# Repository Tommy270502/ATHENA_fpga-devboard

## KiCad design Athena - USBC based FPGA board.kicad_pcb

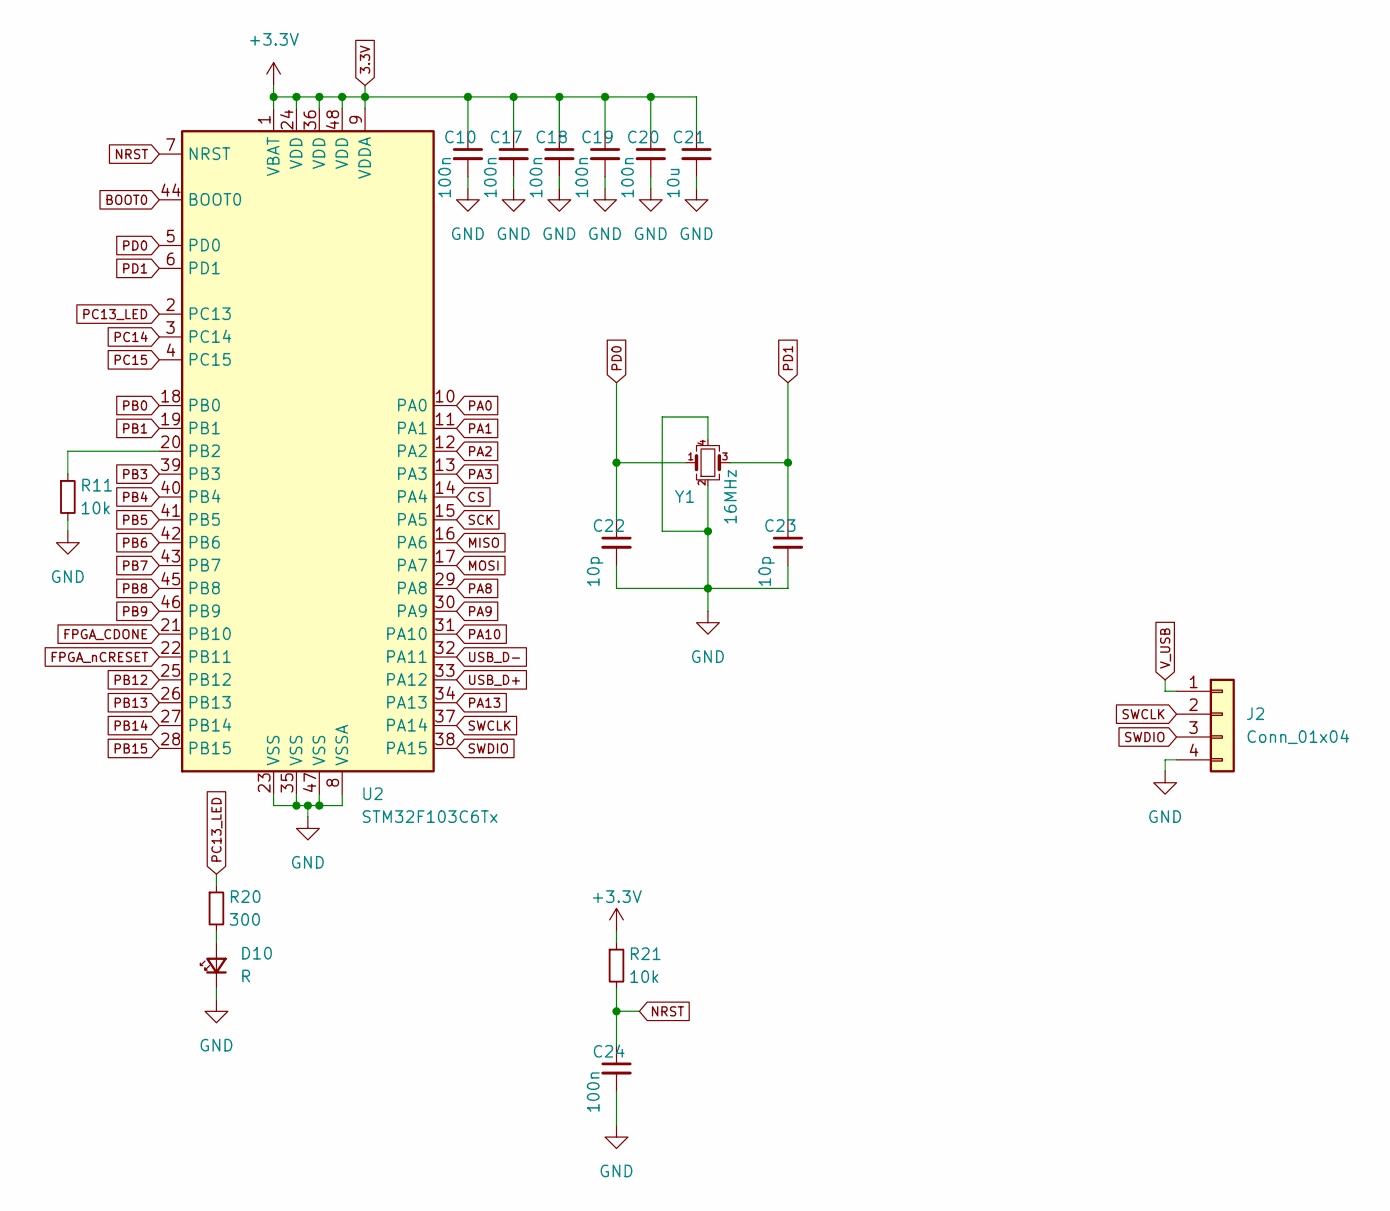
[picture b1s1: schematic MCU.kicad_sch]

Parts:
C10, C17, C18, C19, C20, C24: 100n; C_0603_1608Metric_Pad1.08x0.95mm_HandSolder
C21: 10u; C_0603_1608Metric_Pad1.08x0.95mm_HandSolder
C22, C23: 10p; C_0603_1608Metric_Pad1.08x0.95mm_HandSolder
D10: R; LED_0603_1608Metric_Pad1.05x0.95mm_HandSolder
J2: Conn_01x04; PinHeader_1x04_P2.54mm_Vertical
R11, R21: 10k; R_0603_1608Metric_Pad0.98x0.95mm_HandSolder
R20: 300; R_0603_1608Metric_Pad0.98x0.95mm_HandSolder
U2: STM32F103C6Tx; LQFP-48_7x7mm_P0.5mm
Y1: 16MHz; Crystal_SMD_2520-4Pin_2.5x2.0mm

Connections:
3.3V: C10.1, C17.1, C18.1, C19.1, C20.1, C21.1, R21.1, U2.1 (VBAT), U2.9 (VDDA), U2.24 (VDD), U2.36 (VDD), U2.48 (VDD); also elsewhere on the board
BOOT0: U2.44 (BOOT0)
CS: U2.14 (PA4); also elsewhere on the board
FPGA_CDONE: U2.21 (PB10); also elsewhere on the board
FPGA_nCRESET: U2.22 (PB11); also elsewhere on the board
GND: C10.2, C17.2, C18.2, C19.2, C20.2, C21.2, C22.2, C23.2, C24.2, D10.1 (K), J2.4, R11.2, U2.8 (VSSA), U2.23 (VSS), U2.35 (VSS), U2.47 (VSS), Y1.2, Y1.4; also elsewhere on the board
MISO: U2.16 (PA6); also elsewhere on the board
MOSI: U2.17 (PA7); also elsewhere on the board
NRST: C24.1, R21.2, U2.7 (NRST)
unnamed: D10.2 (A), R20.2
unnamed: R11.1, U2.20 (PB2)
PA0: U2.10 (PA0)
PA1: U2.11 (PA1)
PA2: U2.12 (PA2)
PA3: U2.13 (PA3)
PA8: U2.29 (PA8)
PA9: U2.30 (PA9)
PA10: U2.31 (PA10)
PA13: U2.34 (PA13)
PB0: U2.18 (PB0)
PB1: U2.19 (PB1)
PB3: U2.39 (PB3)
PB4: U2.40 (PB4)
PB5: U2.41 (PB5)
PB6: U2.42 (PB6)
PB7: U2.43 (PB7)
PB8: U2.45 (PB8)
PB9: U2.46 (PB9)
PB12: U2.25 (PB12)
PB13: U2.26 (PB13)
PB14: U2.27 (PB14)
PB15: U2.28 (PB15)
PC13_LED: R20.1, U2.2 (PC13)
PC14: U2.3 (PC14)
PC15: U2.4 (PC15)
PD0: C22.1, U2.5 (PD0), Y1.1
PD1: C23.1, U2.6 (PD1), Y1.3
SCK: U2.15 (PA5); also elsewhere on the board
SWCLK: J2.2, U2.37 (PA14)
SWDIO: J2.3, U2.38 (PA15)
USB_D+: U2.33 (PA12); also elsewhere on the board
USB_D-: U2.32 (PA11); also elsewhere on the board
V_USB: J2.1; also elsewhere on the board

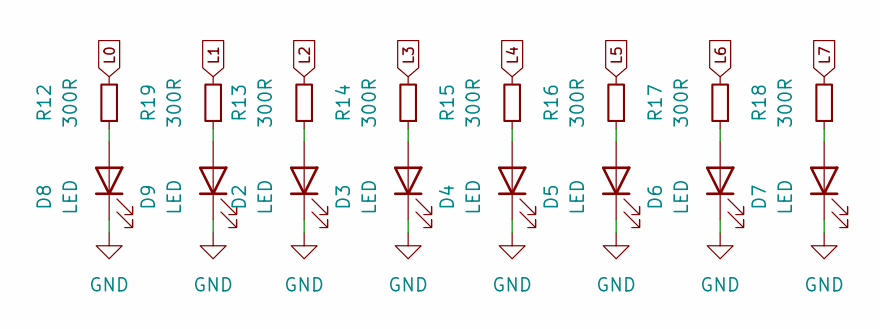
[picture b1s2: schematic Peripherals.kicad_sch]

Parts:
D2, D3, D4, D5, D6, D7, D8, D9: LED; LED_0603_1608Metric_Pad1.05x0.95mm_HandSolder
R12, R13, R14, R15, R16, R17, R18, R19: 300R; R_0603_1608Metric_Pad0.98x0.95mm_HandSolder

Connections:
GND: D2.1 (K), D3.1 (K), D4.1 (K), D5.1 (K), D6.1 (K), D7.1 (K), D8.1 (K), D9.1 (K); also elsewhere on the board
L0: R12.2; also elsewhere on the board
L1: R19.2; also elsewhere on the board
L2: R13.2; also elsewhere on the board
L3: R14.2; also elsewhere on the board
L4: R15.2; also elsewhere on the board
L5: R16.2; also elsewhere on the board
L6: R17.2; also elsewhere on the board
L7: R18.2; also elsewhere on the board
unnamed: D2.2 (A), R13.1
unnamed: D3.2 (A), R14.1
unnamed: D4.2 (A), R15.1
unnamed: D5.2 (A), R16.1
unnamed: D6.2 (A), R17.1
unnamed: D7.2 (A), R18.1
unnamed: D8.2 (A), R12.1
unnamed: D9.2 (A), R19.1

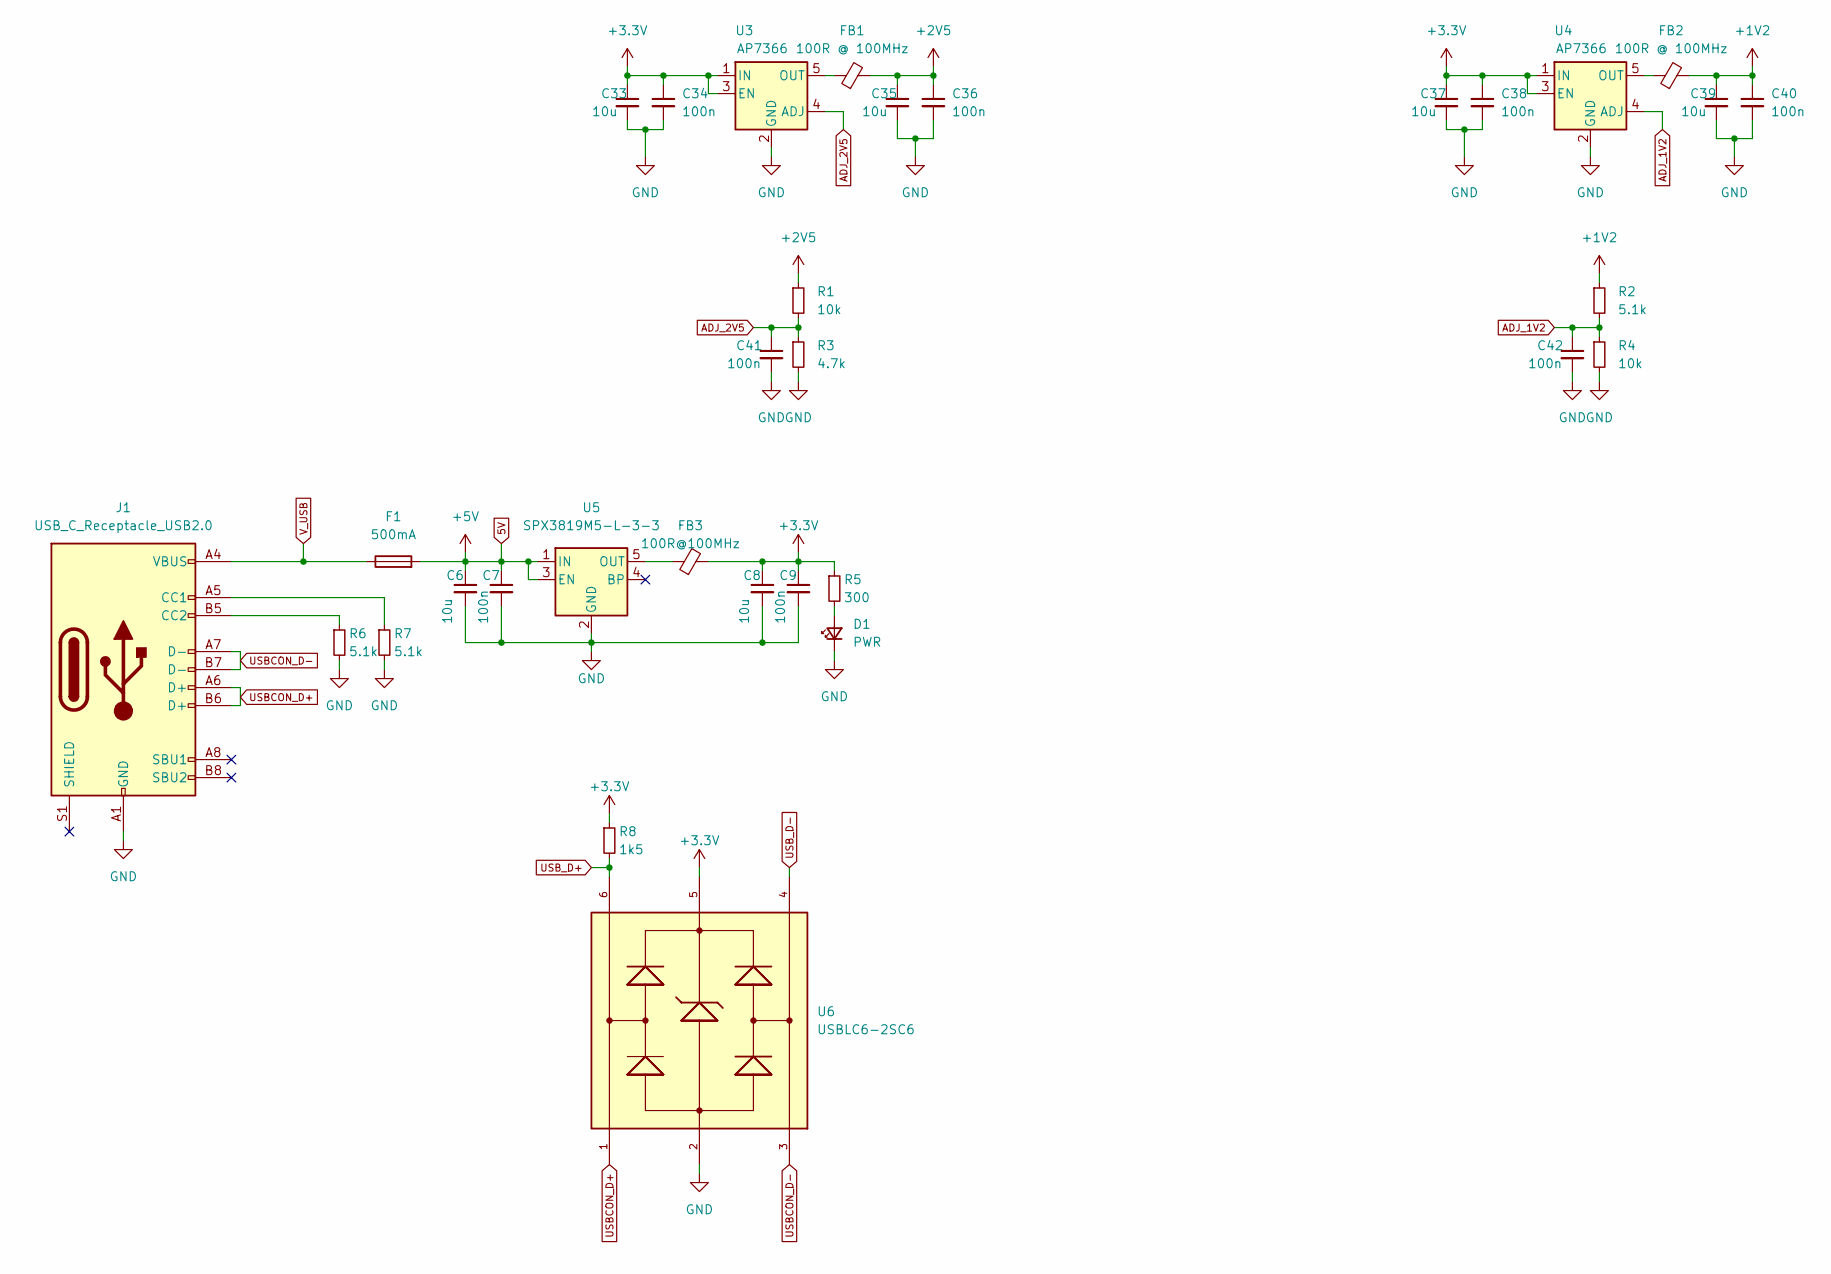
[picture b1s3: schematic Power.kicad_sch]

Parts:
C6, C8, C33, C35, C37, C39: 10u; C_0603_1608Metric_Pad1.08x0.95mm_HandSolder
C7, C9, C34, C36, C38, C40, C41, C42: 100n; C_0603_1608Metric_Pad1.08x0.95mm_HandSolder
D1: PWR; LED_0603_1608Metric_Pad1.05x0.95mm_HandSolder
F1: 500mA; Fuse_0603_1608Metric_Pad1.05x0.95mm_HandSolder
FB1, FB2: 100R @ 100MHz; R_0603_1608Metric_Pad0.98x0.95mm_HandSolder
FB3: 100R@100MHz; L_0603_1608Metric_Pad1.05x0.95mm_HandSolder
J1: USB_C_Receptacle_USB2.0; USB_C_Receptacle_HRO_TYPE-C-31-M-12
R1, R4: 10k; R_0603_1608Metric_Pad0.98x0.95mm_HandSolder
R2, R6, R7: 5.1k; R_0603_1608Metric_Pad0.98x0.95mm_HandSolder
R3: 4.7k; R_0603_1608Metric_Pad0.98x0.95mm_HandSolder
R5: 300; R_0603_1608Metric_Pad0.98x0.95mm_HandSolder
R8: 1k5; R_0603_1608Metric_Pad0.98x0.95mm_HandSolder
U3, U4: AP7366; SOT-23-5
U5: SPX3819M5-L-3-3; SOT-23-5
U6: USBLC6-2SC6; SOT95P280X145-6N

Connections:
3.3V: C8.1, C9.1, C33.1, C34.1, C37.1, C38.1, FB3.2, R5.1, R8.1, U3.1 (IN), U3.3 (EN), U4.1 (IN), U4.3 (EN), U6.5; also elsewhere on the board
5V: C6.1, C7.1, F1.2, U5.1 (IN), U5.3 (EN)
+1V2: C39.1, C40.1, FB2.2, R2.1; also elsewhere on the board
+2V5: C35.1, C36.1, FB1.2, R1.1; also elsewhere on the board
ADJ_1V2: C42.1, R2.2, R4.1, U4.4 (ADJ)
ADJ_2V5: C41.1, R1.2, R3.1, U3.4 (ADJ)
GND: C6.2, C7.2, C8.2, C9.2, C33.2, C34.2, C35.2, C36.2, C37.2, C38.2, C39.2, C40.2, C41.2, C42.2, D1.1 (K), J1.A1 (GND), J1.A12 (GND), J1.B1 (GND), J1.B12 (GND), R3.2, R4.2, R6.2, R7.2, U3.2 (GND), U4.2 (GND), U5.2 (GND), U6.2; also elsewhere on the board
unnamed: D1.2 (A), R5.2
unnamed: FB1.1, U3.5 (OUT)
unnamed: FB2.1, U4.5 (OUT)
unnamed: FB3.1, U5.5 (OUT)
unnamed: J1.A5 (CC1), R7.1
unnamed: J1.B5 (CC2), R6.1
USBCON_D+: J1.A6 (D+), J1.B6 (D+), U6.1
USBCON_D-: J1.A7 (D-), J1.B7 (D-), U6.3
USB_D+: R8.2, U6.6; also elsewhere on the board
USB_D-: U6.4; also elsewhere on the board
V_USB: F1.1, J1.A4 (VBUS), J1.A9 (VBUS), J1.B4 (VBUS), J1.B9 (VBUS); also elsewhere on the board

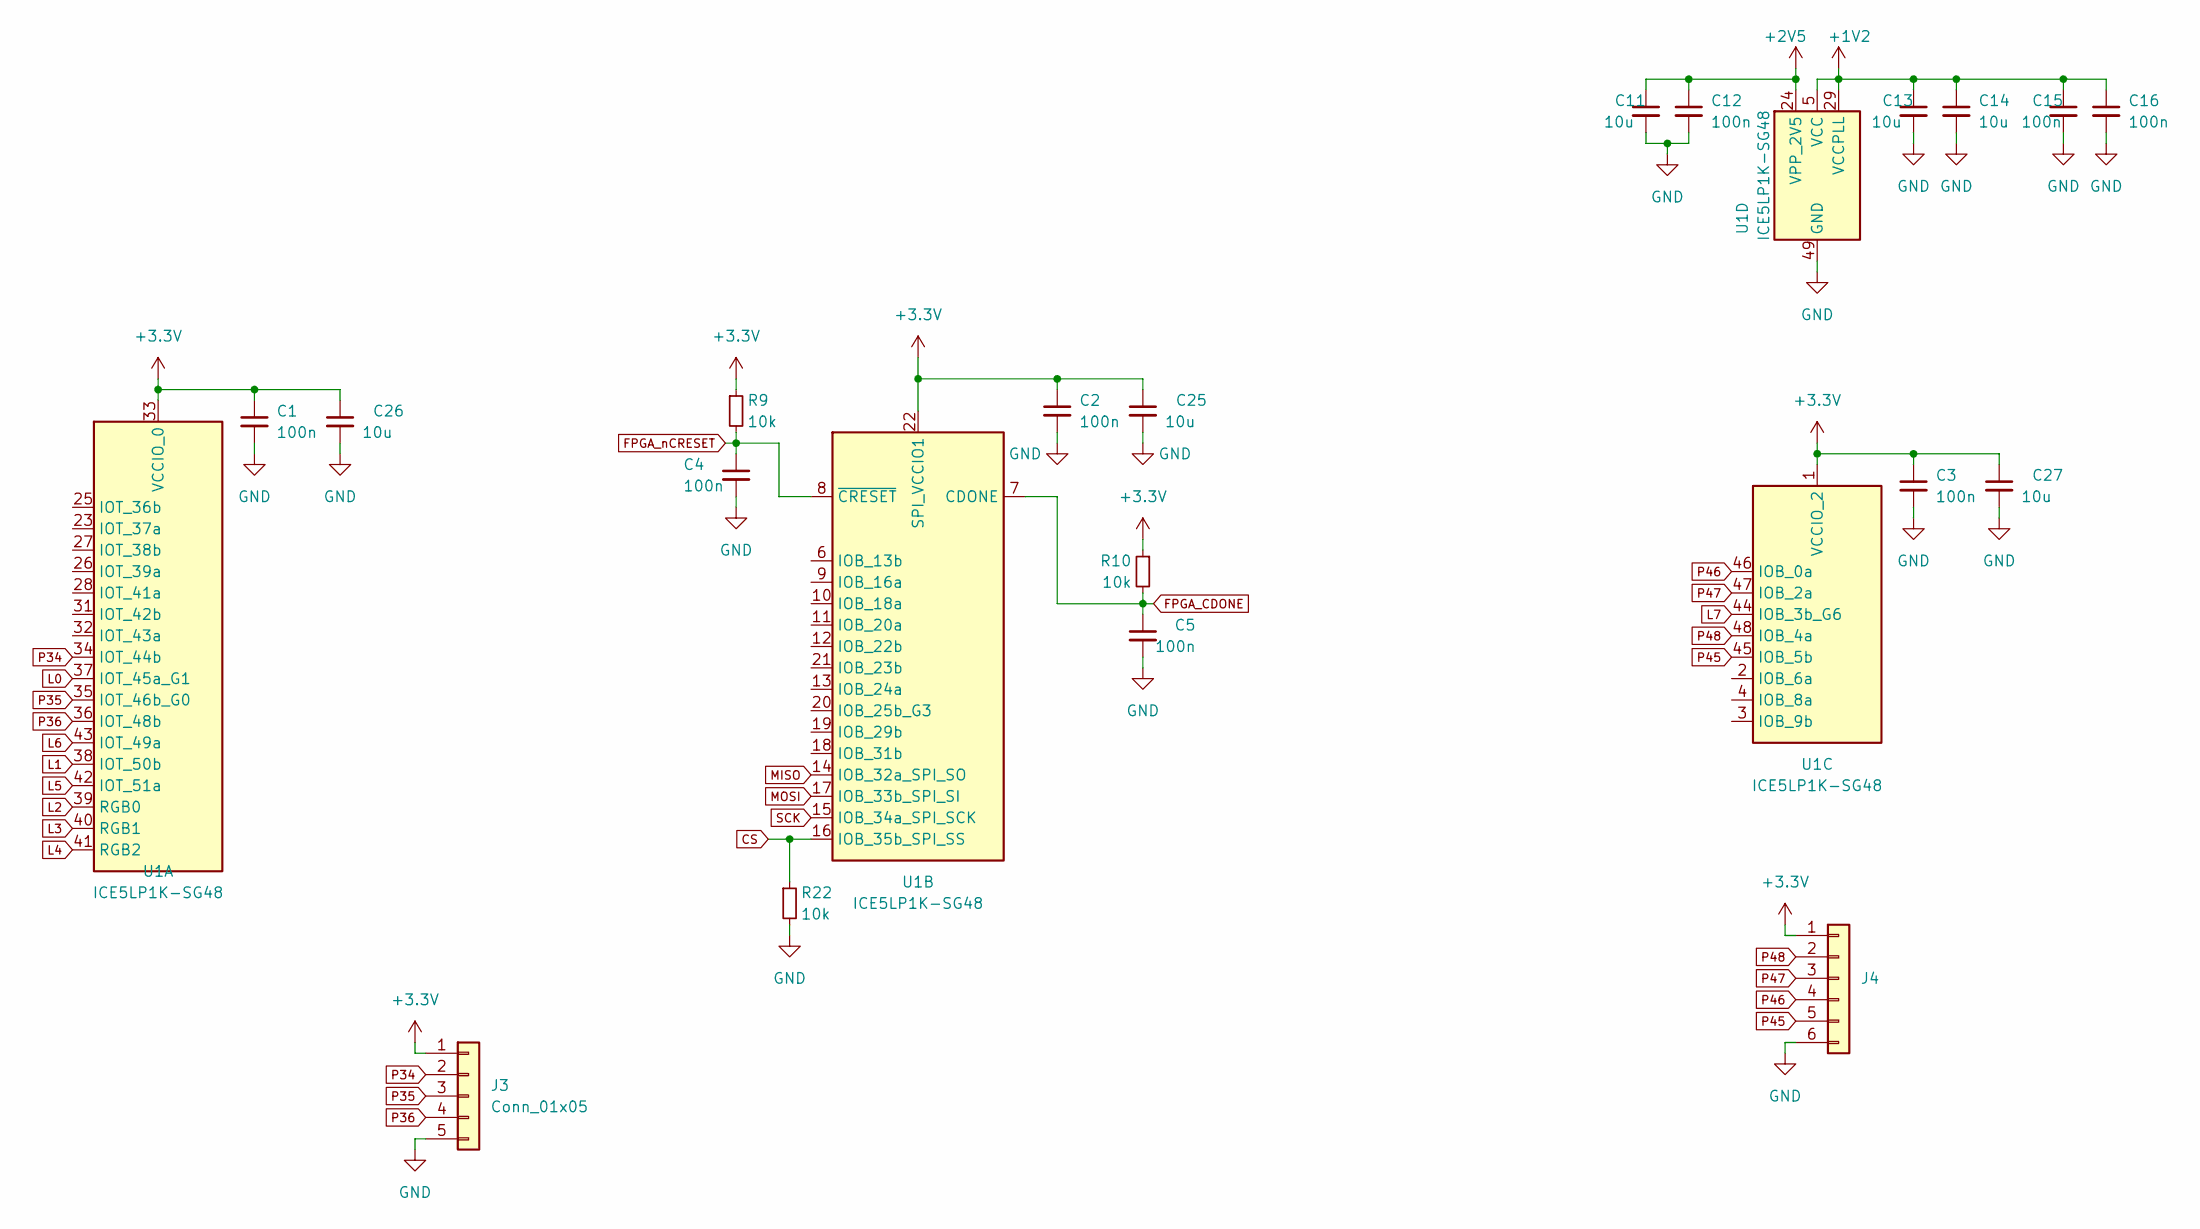
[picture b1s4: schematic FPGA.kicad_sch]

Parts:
C1, C2, C3, C4, C5, C12, C15, C16: 100n; C_0603_1608Metric_Pad1.08x0.95mm_HandSolder
C11, C13, C14, C25, C26, C27: 10u; C_0603_1608Metric_Pad1.08x0.95mm_HandSolder
J3: Conn_01x05; PinHeader_1x05_P2.54mm_Vertical
J4: (no value)
R9, R10, R22: 10k; R_0603_1608Metric_Pad0.98x0.95mm_HandSolder
U1: ICE5LP1K-SG48; QFN-48-1EP_7x7mm_P0.5mm_EP5.6x5.6mm

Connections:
3.3V: C1.1, C2.1, C3.1, C25.1, C26.1, C27.1, J3.1, J4.1, R9.1, R10.1, U1.1 (VCCIO_2), U1.22 (SPI_VCCIO1), U1.33 (VCCIO_0); also elsewhere on the board
+1V2: C13.1, C14.1, C15.1, C16.1, U1.5 (VCC), U1.29 (VCCPLL), U1.30 (VCC); also elsewhere on the board
+2V5: C11.1, C12.1, U1.24 (VPP_2V5); also elsewhere on the board
CS: R22.1, U1.16 (IOB_35b_SPI_SS); also elsewhere on the board
FPGA_CDONE: C5.1, R10.2, U1.7 (CDONE); also elsewhere on the board
FPGA_nCRESET: C4.1, R9.2, U1.8 (~CRESET); also elsewhere on the board
GND: C1.2, C2.2, C3.2, C4.2, C5.2, C11.2, C12.2, C13.2, C14.2, C15.2, C16.2, C25.2, C26.2, C27.2, J3.5, J4.6, R22.2, U1.49 (GND); also elsewhere on the board
L0: U1.37 (IOT_45a_G1); also elsewhere on the board
L1: U1.38 (IOT_50b); also elsewhere on the board
L2: U1.39 (RGB0); also elsewhere on the board
L3: U1.40 (RGB1); also elsewhere on the board
L4: U1.41 (RGB2); also elsewhere on the board
L5: U1.42 (IOT_51a); also elsewhere on the board
L6: U1.43 (IOT_49a); also elsewhere on the board
L7: U1.44 (IOB_3b_G6); also elsewhere on the board
MISO: U1.14 (IOB_32a_SPI_SO); also elsewhere on the board
MOSI: U1.17 (IOB_33b_SPI_SI); also elsewhere on the board
P34: J3.2, U1.34 (IOT_44b)
P35: J3.3, U1.35 (IOT_46b_G0)
P36: J3.4, U1.36 (IOT_48b)
P45: J4.5, U1.45 (IOB_5b)
P46: J4.4, U1.46 (IOB_0a)
P47: J4.3, U1.47 (IOB_2a)
P48: J4.2, U1.48 (IOB_4a)
SCK: U1.15 (IOB_34a_SPI_SCK); also elsewhere on the board

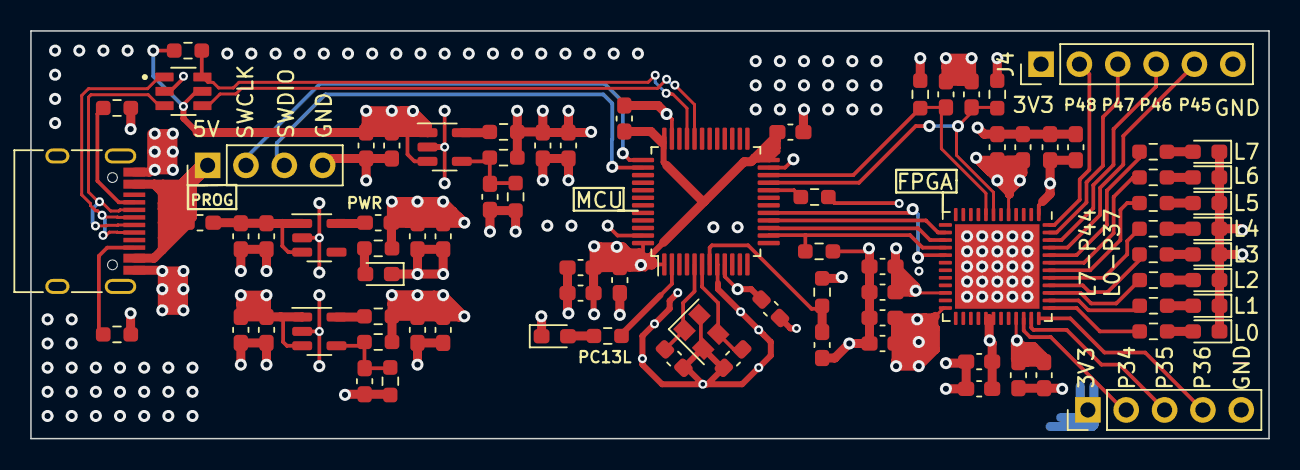
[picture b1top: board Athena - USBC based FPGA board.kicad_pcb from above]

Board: 4 copper layers, 82.0 x 27.0 mm, 84 parts (0 on the bottom side), 55 nets.

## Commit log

2023-01-28 Create LICENSE
